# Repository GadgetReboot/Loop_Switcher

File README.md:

# Loop_Switcher
Guitar Effects Loop Switcher Matrix Board
<br><br><BR><BR>

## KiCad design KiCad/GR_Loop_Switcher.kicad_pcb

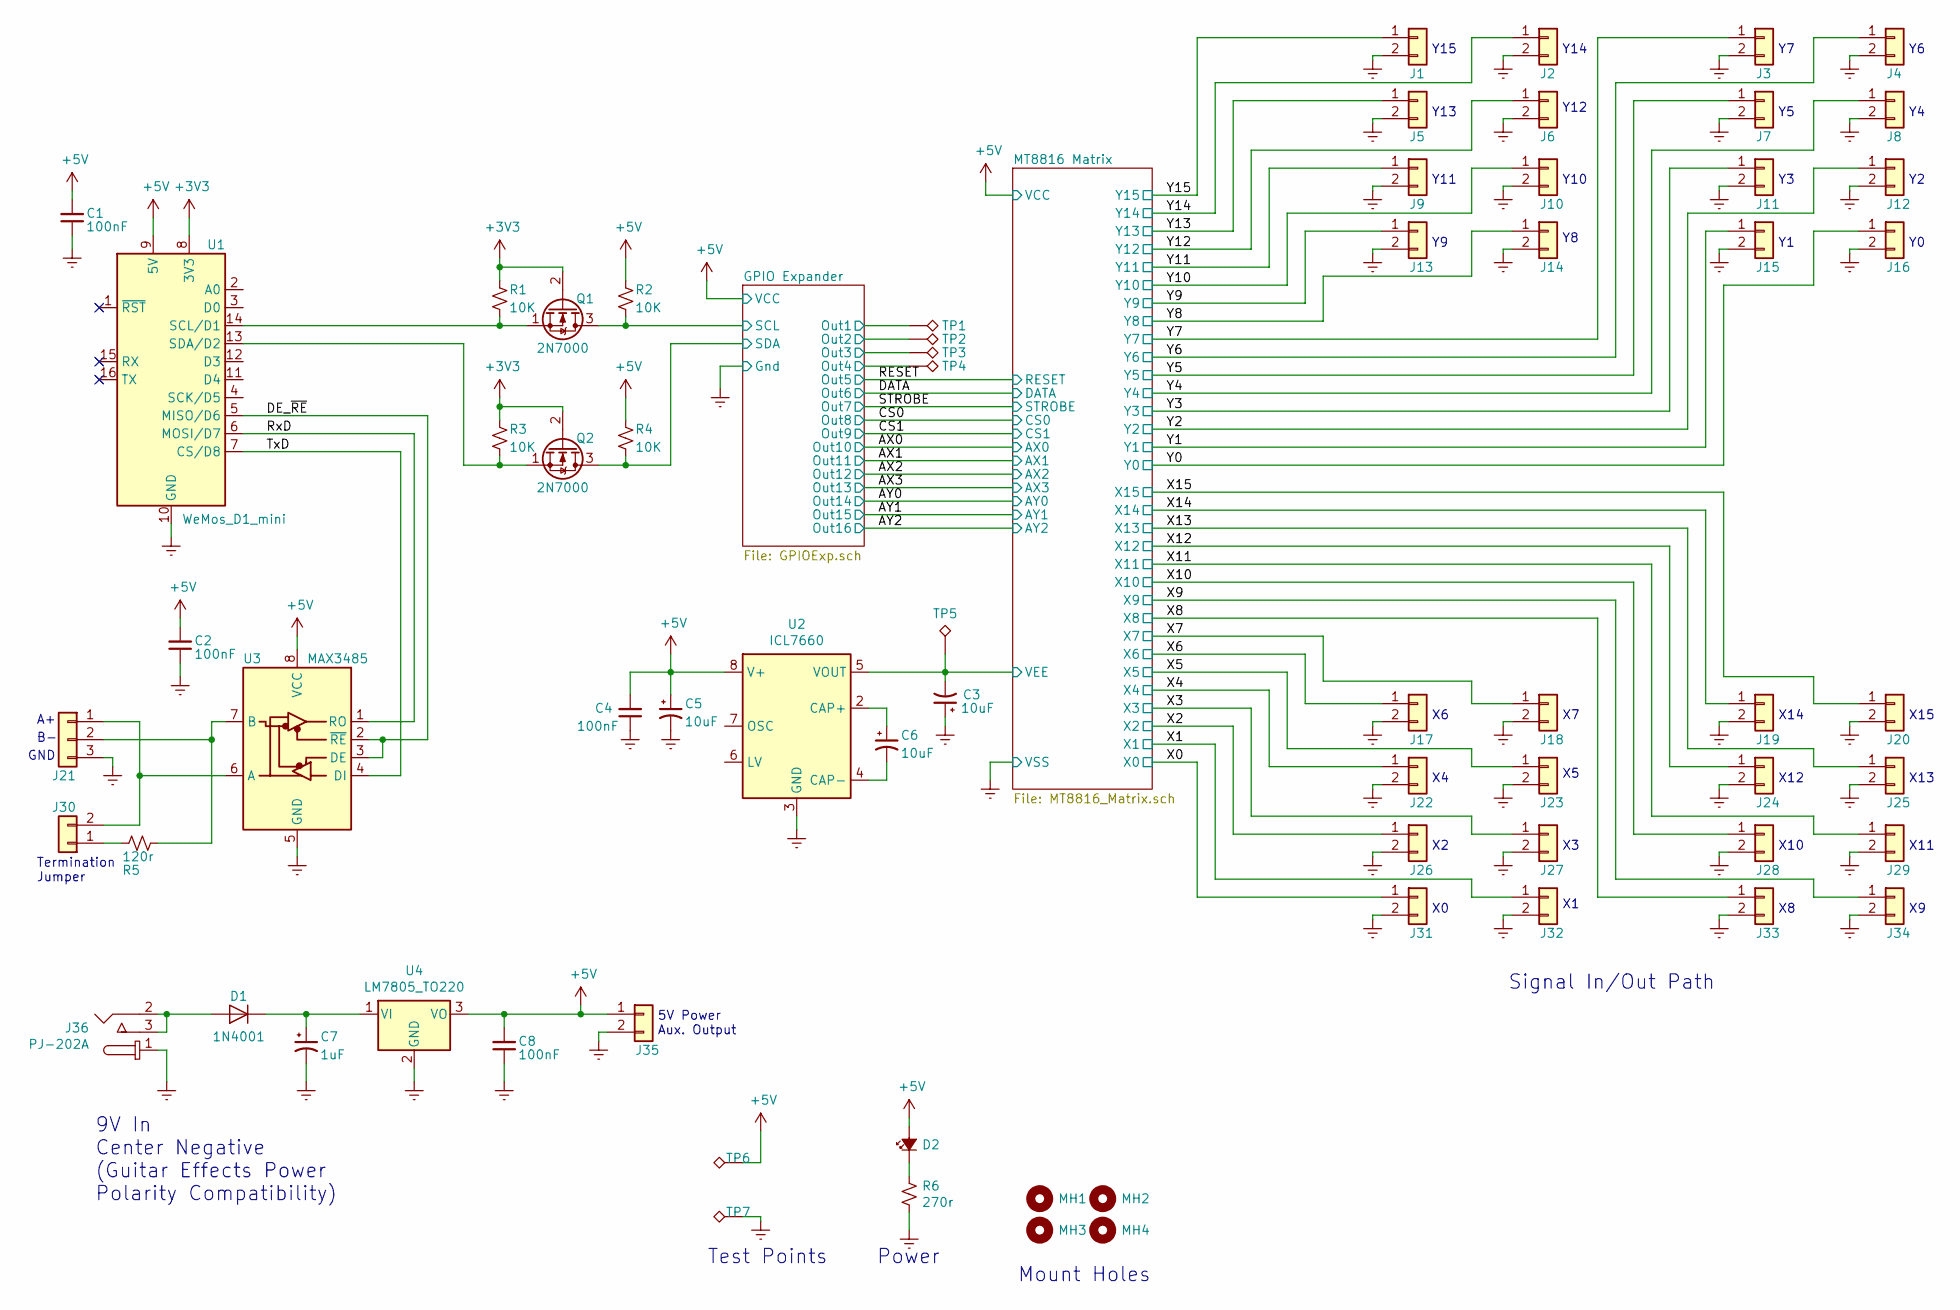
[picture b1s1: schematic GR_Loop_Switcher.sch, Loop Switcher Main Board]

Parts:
C1, C2, C4, C8: 100nF; C_Disc_D3.8mm_W2.6mm_P2.50mm
C3, C5, C6: 10uF; CP_Radial_D5.0mm_P2.50mm
C7: 1uF; CP_Radial_D5.0mm_P2.50mm
D1: 1N4001; D_DO-41_SOD81_P10.16mm_Horizontal
D2: LED_Small_ALT; LED_D5.0mm
J1, J2, J3, J4, J5, J6, J7, J8, J9, J10, J11, J12, J13, J14, J15, J16, J17, J18, J19, J20, J22, J23, J24, J25, J26, J27, J28, J29, J31, J32, J33, J34, J35: Conn_01x02; JST_XH_B2B-XH-A_1x02_P2.50mm_Vertical
J21: Conn_01x03; JST_XH_B3B-XH-A_1x03_P2.50mm_Vertical
J30: Conn_01x02; PinHeader_1x02_P2.54mm_Vertical
J36: PJ-202A; Barrel_Jack_5.5mmODx2.1mmID_PJ-202A; MPN PJ-202A; Digi-Key_PN CP-202A-ND
MH1, MH2, MH3, MH4: MountingHole; MountingHole_3.2mm_M3
Q1, Q2: 2N7000; TO-92_Inline
R1, R2, R3, R4: 10K; R_Axial_DIN0207_L6.3mm_D2.5mm_P10.16mm_Horizontal
R5: 120r; R_Axial_DIN0207_L6.3mm_D2.5mm_P10.16mm_Horizontal
R6: 270r; R_Axial_DIN0207_L6.3mm_D2.5mm_P10.16mm_Horizontal
TP1, TP2, TP3, TP4, TP5, TP6, TP7: TestPoint_Alt; TestPoint_THTPad_D2.0mm_Drill1.0mm
U1: WeMos_D1_mini; WEMOS_D1_mini_light
U2: ICL7660; DIP-8_W7.62mm_LongPads
U3: MAX3485; DIP-8_W7.62mm_LongPads
U4: LM7805_TO220; TO-220-3_Vertical

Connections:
+3V3: Q1.2 (G), Q2.2 (G), R1.1, R3.1, U1.8 (3V3)
+5V: C1.2, C2.2, C4.2, C5.1, C8.2, D2.2 (A), J35.1, R2.1, R4.1, TP6.1, U1.9 (5V), U2.8 (V+), U3.8 (VCC), U4.3 (VO); also elsewhere on the board
/DE_~RE: U1.5 (MISO/D6), U3.2 (~RE), U3.3 (DE)
/GPIO Expander/Out1: TP1.1; also elsewhere on the board
/GPIO Expander/Out2: TP2.1; also elsewhere on the board
/GPIO Expander/Out3: TP3.1; also elsewhere on the board
/GPIO Expander/Out4: TP4.1; also elsewhere on the board
/GPIO Expander/SCL: Q1.3 (D), R2.2; also elsewhere on the board
/GPIO Expander/SDA: Q2.3 (D), R4.2; also elsewhere on the board
/RxD: U1.6 (MOSI/D7), U3.1 (RO)
/TxD: U1.7 (CS/D8), U3.4 (DI)
/X0: J31.1; also elsewhere on the board
/X1: J32.1; also elsewhere on the board
/X2: J26.1; also elsewhere on the board
/X3: J27.1; also elsewhere on the board
/X4: J22.1; also elsewhere on the board
/X5: J23.1; also elsewhere on the board
/X6: J17.1; also elsewhere on the board
/X7: J18.1; also elsewhere on the board
/X8: J33.1; also elsewhere on the board
/X9: J34.1; also elsewhere on the board
/X10: J28.1; also elsewhere on the board
/X11: J29.1; also elsewhere on the board
/X12: J24.1; also elsewhere on the board
/X13: J25.1; also elsewhere on the board
/X14: J19.1; also elsewhere on the board
/X15: J20.1; also elsewhere on the board
/Y0: J16.1; also elsewhere on the board
/Y1: J15.1; also elsewhere on the board
/Y2: J12.1; also elsewhere on the board
/Y3: J11.1; also elsewhere on the board
/Y4: J8.1; also elsewhere on the board
/Y5: J7.1; also elsewhere on the board
/Y6: J4.1; also elsewhere on the board
/Y7: J3.1; also elsewhere on the board
/Y8: J14.1; also elsewhere on the board
/Y9: J13.1; also elsewhere on the board
/Y10: J10.1; also elsewhere on the board
/Y11: J9.1; also elsewhere on the board
/Y12: J6.1; also elsewhere on the board
/Y13: J5.1; also elsewhere on the board
/Y14: J2.1; also elsewhere on the board
/Y15: J1.1; also elsewhere on the board
GNDREF: C1.1, C2.1, C3.1, C4.1, C5.2, C7.2, C8.1, J1.2, J2.2, J3.2, J4.2, J5.2, J6.2, J7.2, J8.2, J9.2, J10.2, J11.2, J12.2, J13.2, J14.2, J15.2, J16.2, J17.2, J18.2, J19.2, J20.2, J21.3, J22.2, J23.2, J24.2, J25.2, J26.2, J27.2, J28.2, J29.2, J31.2, J32.2, J33.2, J34.2, J35.2, J36.1, R6.2, TP7.1, U1.10 (GND), U2.3 (GND), U3.5 (GND), U4.2 (GND); also elsewhere on the board
unnamed: C6.1, U2.2 (CAP+)
unnamed: C6.2, U2.4 (CAP-)
unnamed: C7.1, D1.1 (K), U4.1 (VI)
unnamed: D1.2 (A), J36.2, J36.3
unnamed: D2.1 (K), R6.1
unnamed: J21.1, J30.2, U3.6 (A)
unnamed: J21.2, R5.1, U3.7 (B)
unnamed: J30.1, R5.2
unnamed: Q1.1 (S), R1.2, U1.14 (SCL/D1)
unnamed: Q2.1 (S), R3.2, U1.13 (SDA/D2)
VEE: C3.2, TP5.1, U2.5 (VOUT); also elsewhere on the board

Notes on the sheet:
Mount Holes
Test Points
Signal In/Out Path
Power
9V In Center Negative (Guitar Effects Power Polarity Compatibility)
GND
Termination Jumper
Y15
Y14
Y13
Y12
Y11
Y10
X14
X15
X12
X13
X10
X11
5V Power Aux. Output

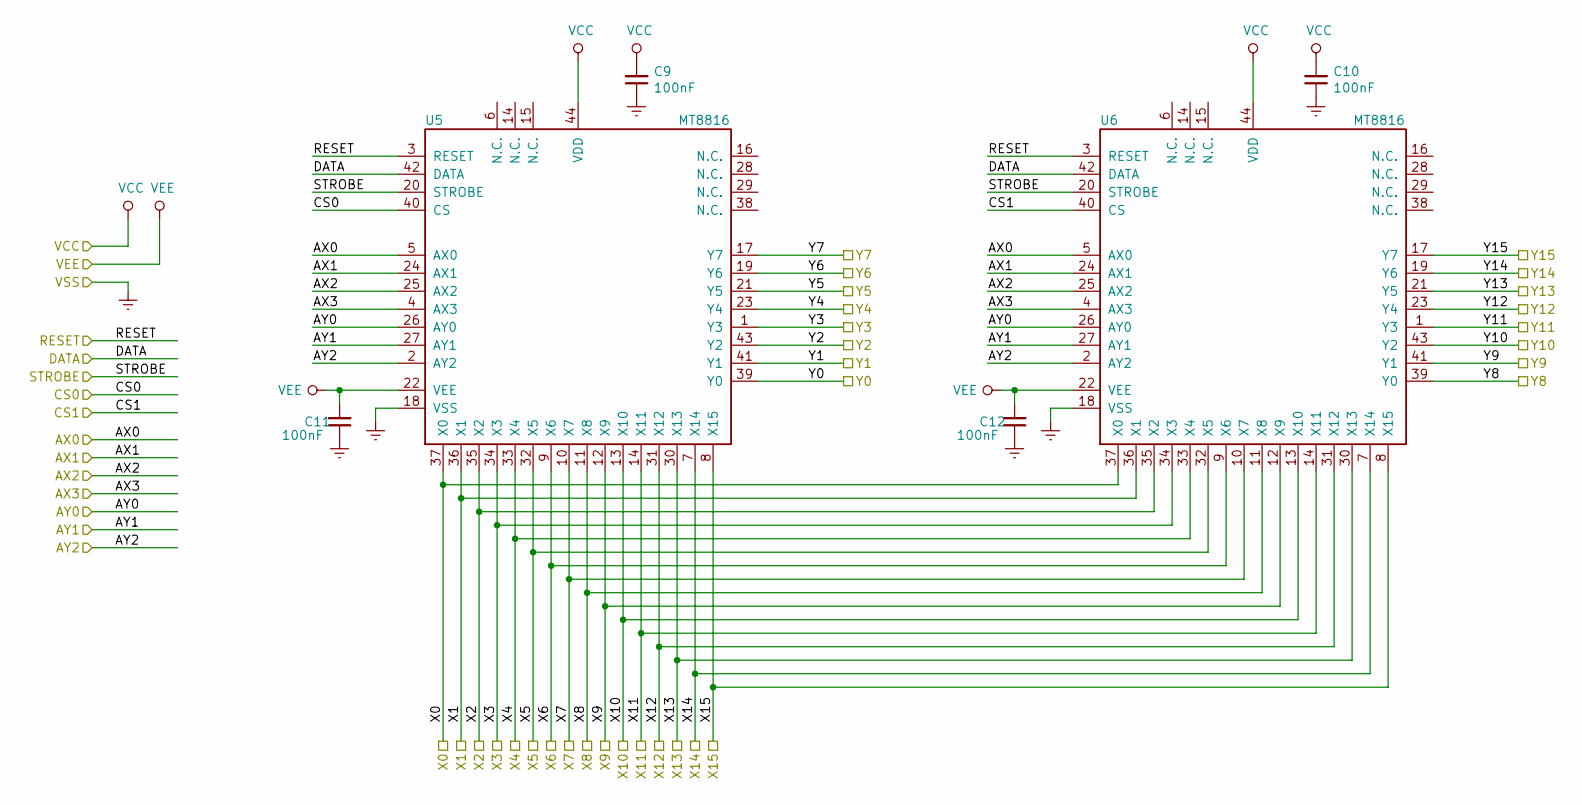
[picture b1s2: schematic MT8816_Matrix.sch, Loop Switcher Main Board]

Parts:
C9, C10, C11, C12: 100nF; C_Disc_D3.8mm_W2.6mm_P2.50mm
U5, U6: MT8816; PLCC-44_THT-Socket

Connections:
+5V: C9.2, C10.2, U5.44 (VDD), U6.44 (VDD); also elsewhere on the board
/AX0: U5.5 (AX0), U6.5 (AX0); also elsewhere on the board
/AX1: U5.24 (AX1), U6.24 (AX1); also elsewhere on the board
/AX2: U5.25 (AX2), U6.25 (AX2); also elsewhere on the board
/AX3: U5.4 (AX3), U6.4 (AX3); also elsewhere on the board
/AY0: U5.26 (AY0), U6.26 (AY0); also elsewhere on the board
/AY1: U5.27 (AY1), U6.27 (AY1); also elsewhere on the board
/AY2: U5.2 (AY2), U6.2 (AY2); also elsewhere on the board
/CS0: U5.40 (CS); also elsewhere on the board
/CS1: U6.40 (CS); also elsewhere on the board
/DATA: U5.42 (DATA), U6.42 (DATA); also elsewhere on the board
/RESET: U5.3 (RESET), U6.3 (RESET); also elsewhere on the board
/STROBE: U5.20 (STROBE), U6.20 (STROBE); also elsewhere on the board
/X0: U5.37 (X0), U6.37 (X0); also elsewhere on the board
/X1: U5.36 (X1), U6.36 (X1); also elsewhere on the board
/X2: U5.35 (X2), U6.35 (X2); also elsewhere on the board
/X3: U5.34 (X3), U6.34 (X3); also elsewhere on the board
/X4: U5.33 (X4), U6.33 (X4); also elsewhere on the board
/X5: U5.32 (X5), U6.32 (X5); also elsewhere on the board
/X6: U5.9 (X6), U6.9 (X6); also elsewhere on the board
/X7: U5.10 (X7), U6.10 (X7); also elsewhere on the board
/X8: U5.11 (X8), U6.11 (X8); also elsewhere on the board
/X9: U5.12 (X9), U6.12 (X9); also elsewhere on the board
/X10: U5.13 (X10), U6.13 (X10); also elsewhere on the board
/X11: U5.14 (N.C.), U6.14 (N.C.); also elsewhere on the board
/X12: U5.31 (X12), U6.31 (X12); also elsewhere on the board
/X13: U5.30 (X13), U6.30 (X13); also elsewhere on the board
/X14: U5.7 (X14), U6.7 (X14); also elsewhere on the board
/X15: U5.8 (X15), U6.8 (X15); also elsewhere on the board
/Y0: U5.39 (Y0); also elsewhere on the board
/Y1: U5.41 (Y1); also elsewhere on the board
/Y2: U5.43 (Y2); also elsewhere on the board
/Y3: U5.1 (Y3); also elsewhere on the board
/Y4: U5.23 (Y4); also elsewhere on the board
/Y5: U5.21 (Y5); also elsewhere on the board
/Y6: U5.19 (Y6); also elsewhere on the board
/Y7: U5.17 (Y7); also elsewhere on the board
/Y8: U6.39 (Y0); also elsewhere on the board
/Y9: U6.41 (Y1); also elsewhere on the board
/Y10: U6.43 (Y2); also elsewhere on the board
/Y11: U6.1 (Y3); also elsewhere on the board
/Y12: U6.23 (Y4); also elsewhere on the board
/Y13: U6.21 (Y5); also elsewhere on the board
/Y14: U6.19 (Y6); also elsewhere on the board
/Y15: U6.17 (Y7); also elsewhere on the board
GNDREF: C9.1, C10.1, C11.1, C12.1, U5.18 (VSS), U6.18 (VSS); also elsewhere on the board
VEE: C11.2, C12.2, U5.22 (VEE), U6.22 (VEE); also elsewhere on the board

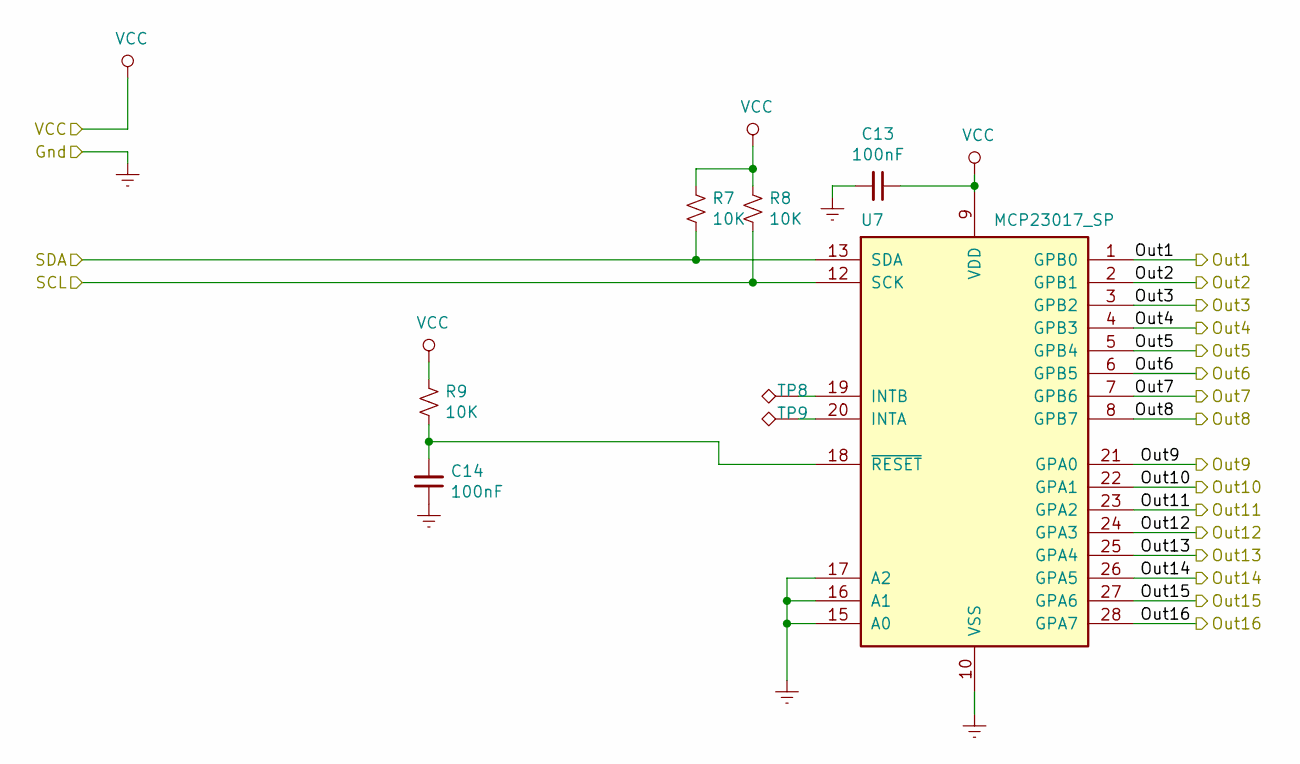
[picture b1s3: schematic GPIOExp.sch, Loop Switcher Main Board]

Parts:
C13, C14: 100nF; C_Disc_D3.8mm_W2.6mm_P2.50mm
R7, R8, R9: 10K; R_Axial_DIN0207_L6.3mm_D2.5mm_P10.16mm_Horizontal
TP8, TP9: TestPoint_Alt; TestPoint_THTPad_D2.0mm_Drill1.0mm
U7: MCP23017_SP; DIP-28_W7.62mm

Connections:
+5V: C13.1, R7.1, R8.1, R9.1, U7.9 (VDD); also elsewhere on the board
/AX0: U7.22 (GPA1); also elsewhere on the board
/AX1: U7.23 (GPA2); also elsewhere on the board
/AX2: U7.24 (GPA3); also elsewhere on the board
/AX3: U7.25 (GPA4); also elsewhere on the board
/AY0: U7.26 (GPA5); also elsewhere on the board
/AY1: U7.27 (GPA6); also elsewhere on the board
/AY2: U7.28 (GPA7); also elsewhere on the board
/CS0: U7.8 (GPB7); also elsewhere on the board
/CS1: U7.21 (GPA0); also elsewhere on the board
/DATA: U7.6 (GPB5); also elsewhere on the board
/GPIO Expander/Out1: U7.1 (GPB0); also elsewhere on the board
/GPIO Expander/Out2: U7.2 (GPB1); also elsewhere on the board
/GPIO Expander/Out3: U7.3 (GPB2); also elsewhere on the board
/GPIO Expander/Out4: U7.4 (GPB3); also elsewhere on the board
/GPIO Expander/SCL: R8.2, U7.12 (SCK); also elsewhere on the board
/GPIO Expander/SDA: R7.2, U7.13 (SDA); also elsewhere on the board
/RESET: U7.5 (GPB4); also elsewhere on the board
/STROBE: U7.7 (GPB6); also elsewhere on the board
GNDREF: C13.2, C14.1, U7.10 (VSS), U7.15 (A0), U7.16 (A1), U7.17 (A2); also elsewhere on the board
unnamed: C14.2, R9.2, U7.18 (~RESET~)
unnamed: TP8.1, U7.19 (INTB)
unnamed: TP9.1, U7.20 (INTA)

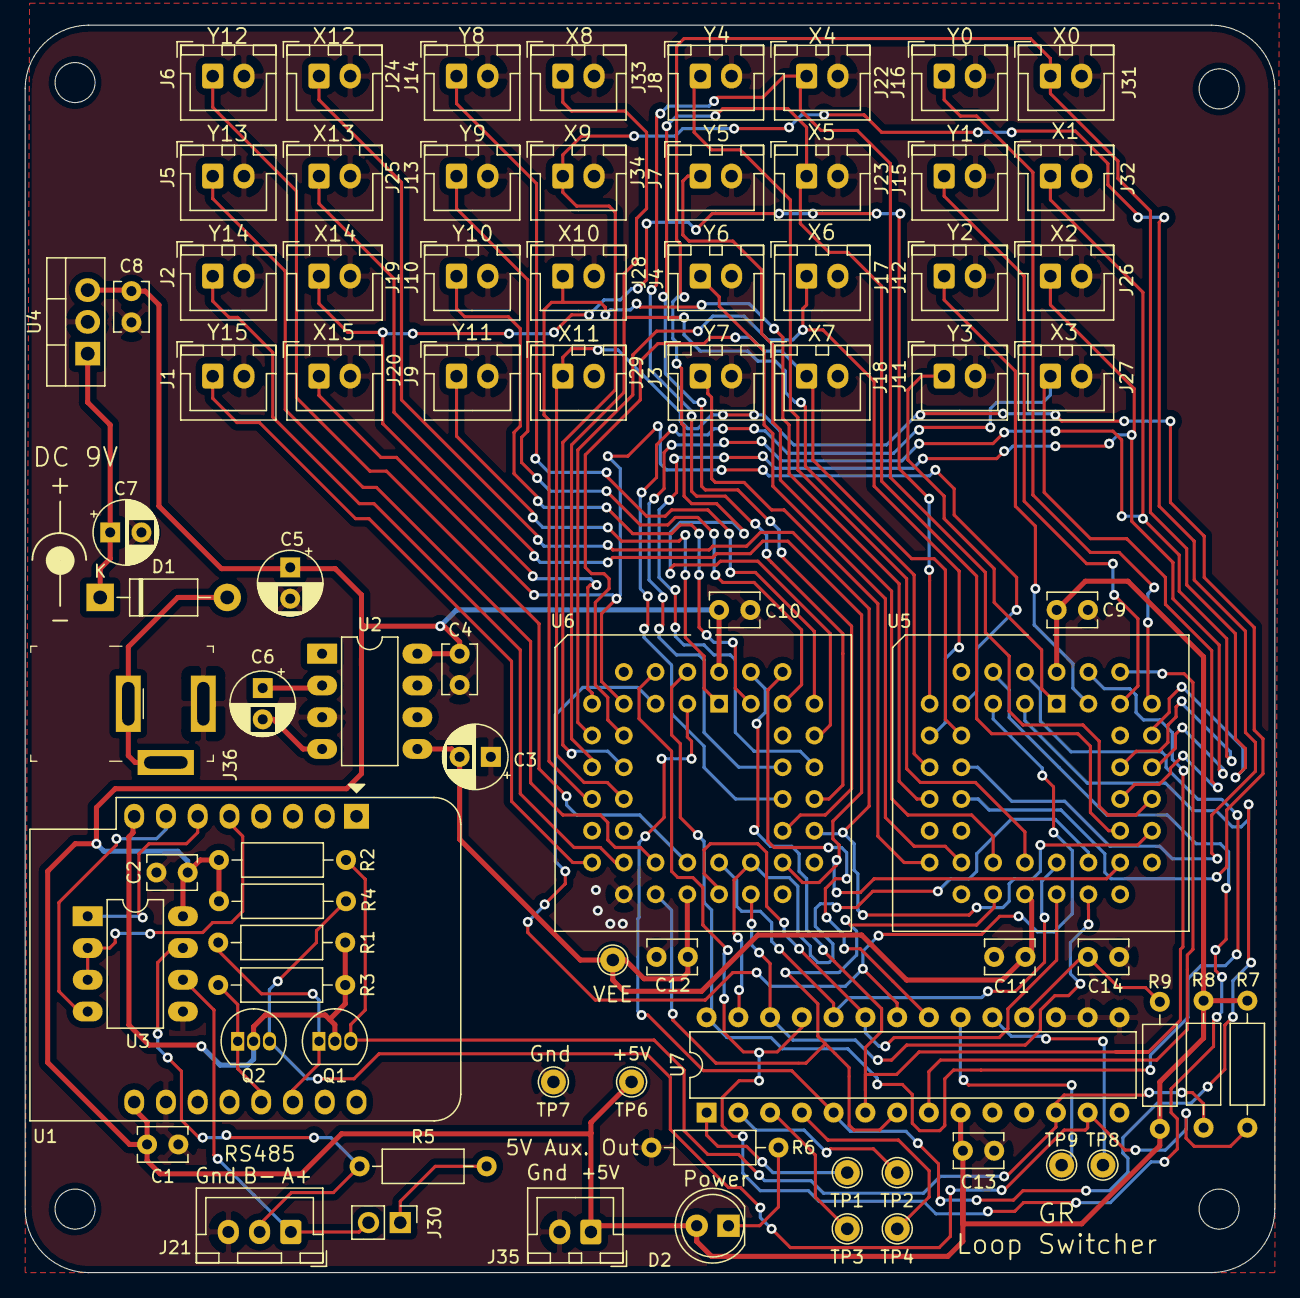
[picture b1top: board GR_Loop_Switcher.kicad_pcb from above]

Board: 2 copper layers, 99.9 x 99.8 mm, 83 parts (0 on the bottom side), 70 nets.
